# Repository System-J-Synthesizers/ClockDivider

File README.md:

# ClockDivider
DIN Sync Clock Divider

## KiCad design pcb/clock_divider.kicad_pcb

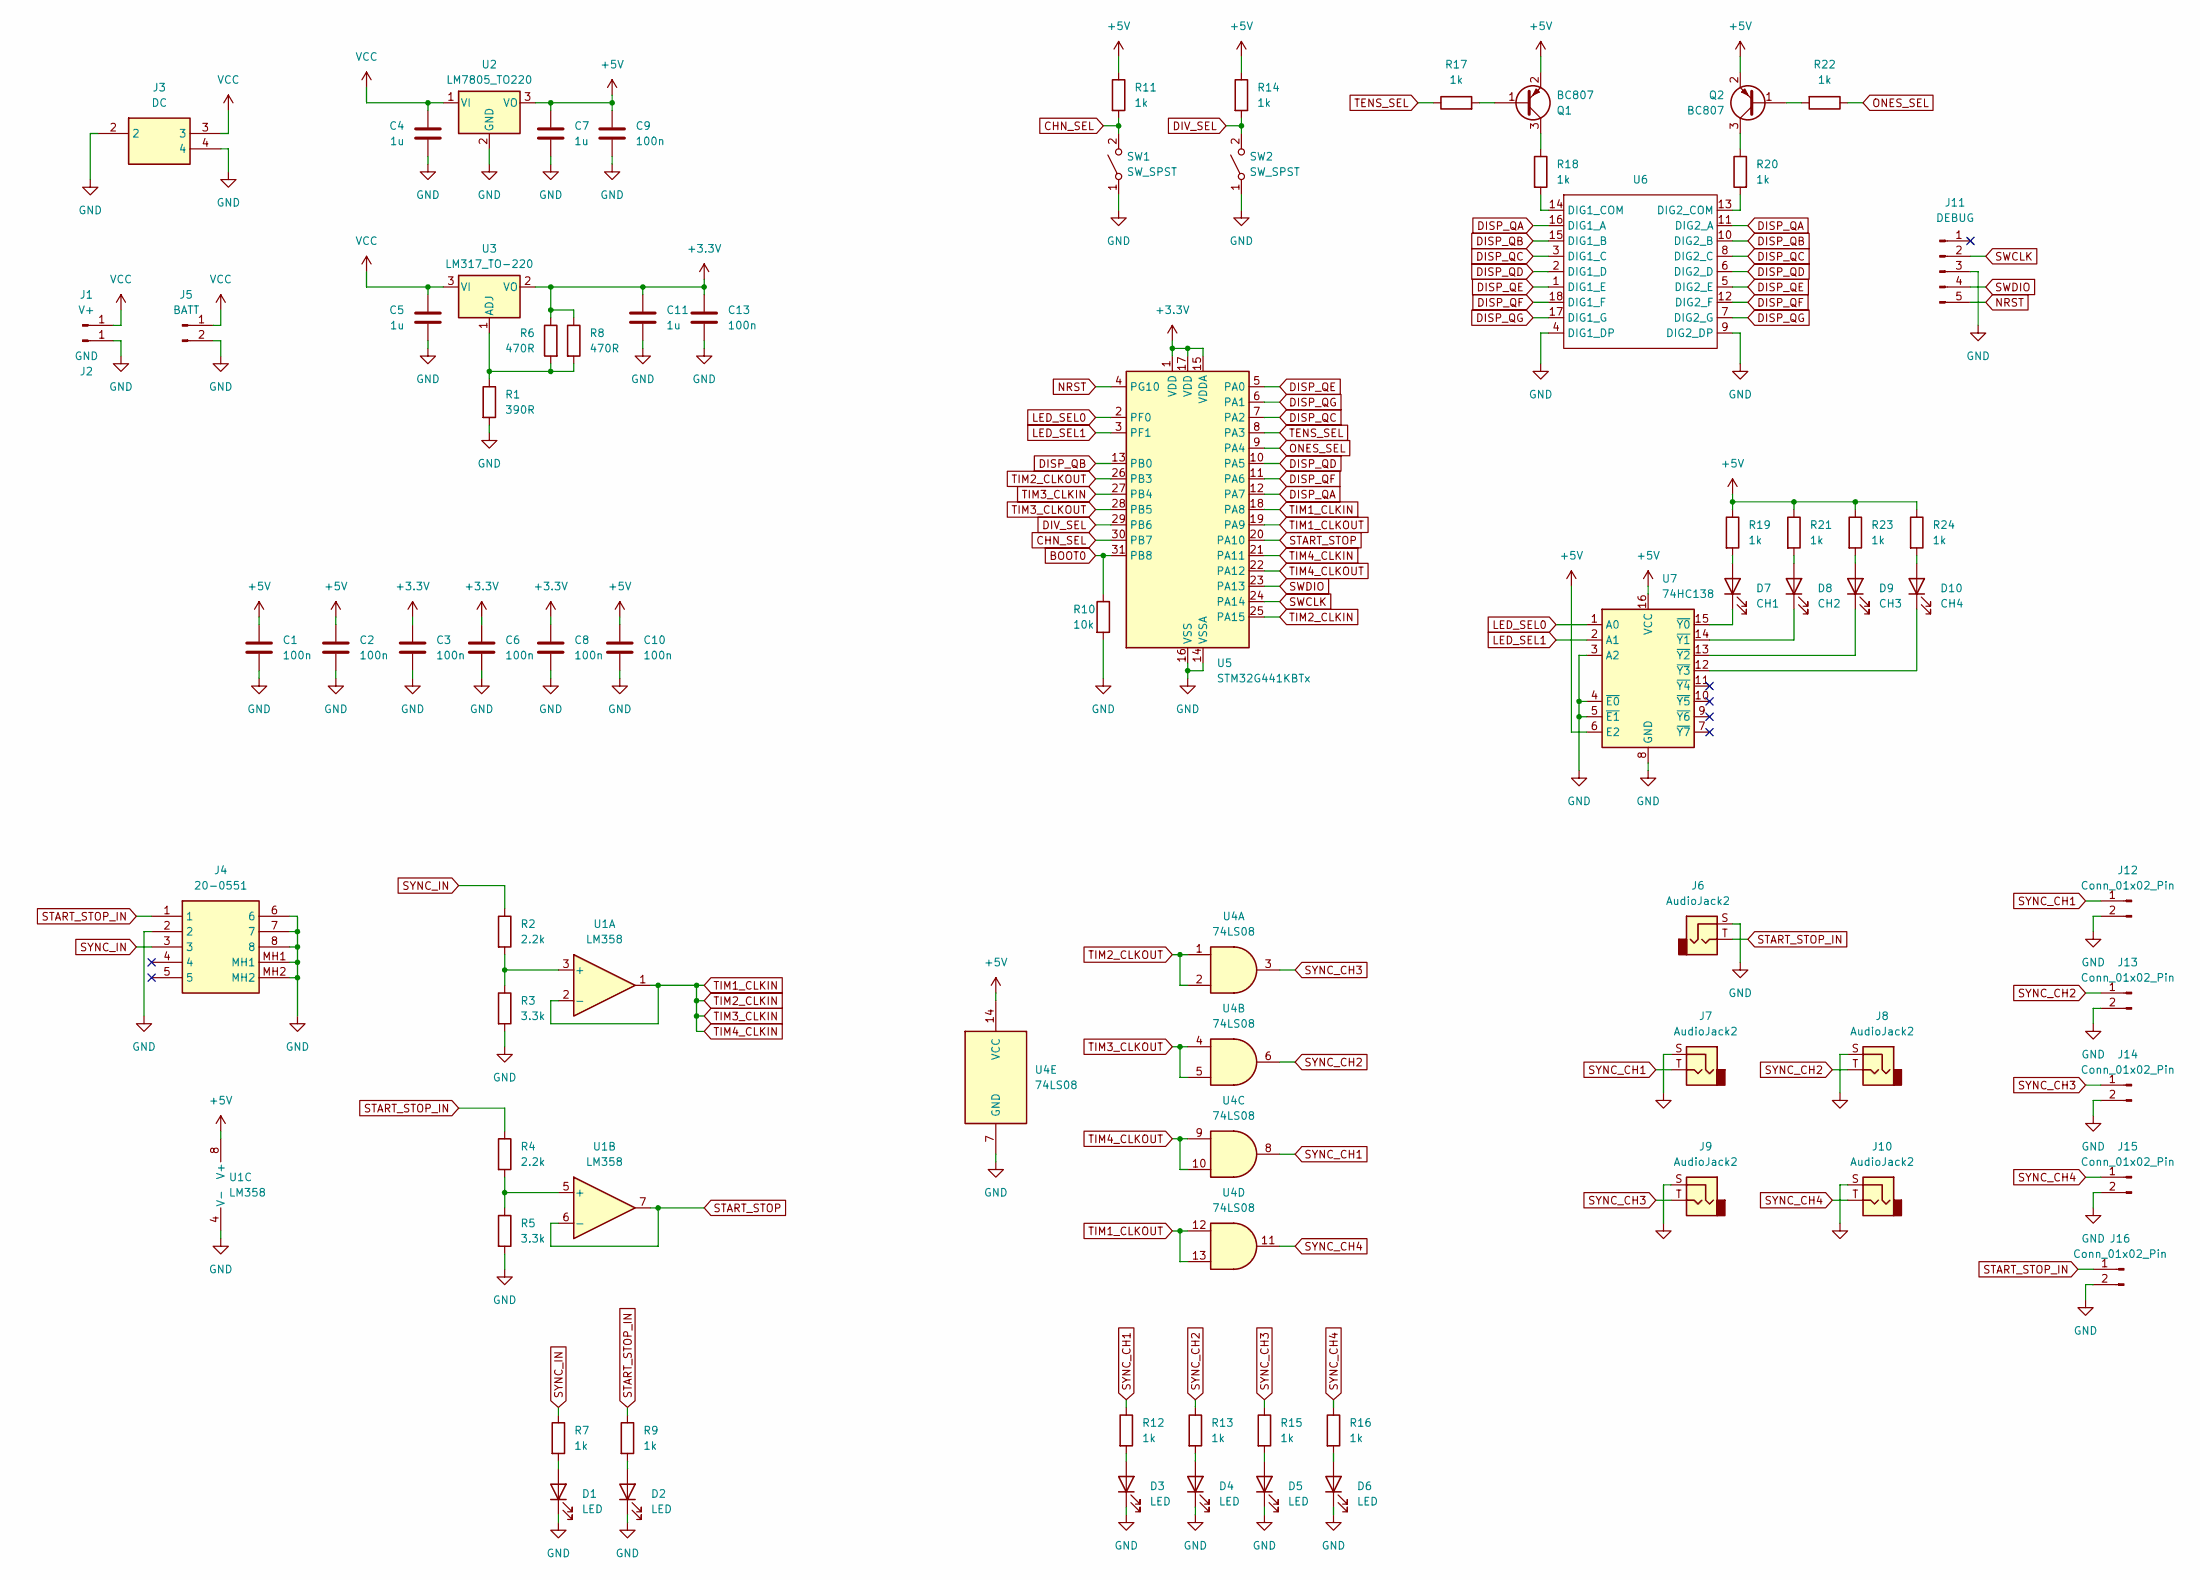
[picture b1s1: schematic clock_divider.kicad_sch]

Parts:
C1, C2, C3, C6, C8, C9, C10, C13: 100n; C_0603_1608Metric
C4, C5, C7, C11: 1u; C_0603_1608Metric
D1, D2, D3, D4, D5, D6: LED; LED_0603_1608Metric
D7: CH1; LED_0603_1608Metric
D8: CH2; LED_0603_1608Metric
D9: CH3; LED_0603_1608Metric
D10: CH4; LED_0603_1608Metric
J1: V+; PinHeader_1x01_P2.54mm_Vertical
J2: GND; PinHeader_1x01_P2.54mm_Vertical
J3: DC; 200975; Manufacturer_Part_Number 20-0975
J4: 20-0551; 200551; Manufacturer_Part_Number 20-0551
J5: BATT; PinHeader_1x02_P2.54mm_Vertical
J6, J7, J8, J9, J10: AudioJack2; Jack_3.5mm_QingPu_WQP-PJ398SM_Vertical
J11: DEBUG; PinHeader_1x05_P2.54mm_Vertical
J12, J13, J14, J15, J16: Conn_01x02_Pin; PinHeader_1x02_P2.54mm_Vertical
Q1, Q2: BC807; SOT-23
R1: 390R; R_0603_1608Metric
R2, R4: 2.2k; R_0603_1608Metric
R3, R5: 3.3k; R_0603_1608Metric
R6, R8: 470R; R_0603_1608Metric
R7, R9, R11, R12, R13, R14, R15, R16, R17, R18, R19, R20, R21, R22, R23, R24: 1k; R_0603_1608Metric
R10: 10k; R_0603_1608Metric
SW1, SW2: SW_SPST; SW_PUSH_6mm
U1: LM358; SOIC-8_3.9x4.9mm_P1.27mm
U2: LM7805_TO220; TO-220-3_Vertical
U3: LM317_TO-220; TO-220-3_Vertical
U4: 74LS08; DIP-14_W7.62mm
U5: STM32G441KBTx; LQFP-32_7x7mm_P0.8mm
U6: OSL20561
U7: 74HC138; DIP-16_W7.62mm

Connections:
+3.3V: C3.1, C6.1, C8.1, C11.1, C13.1, R6.1, R8.1, U3.2 (VO), U5.1 (VDD), U5.15 (VDDA), U5.17 (VDD)
+5V: C1.1, C2.1, C7.1, C9.1, C10.1, Q1.2 (E), Q2.2 (E), R11.1, R14.1, R19.1, R21.1, R23.1, R24.1, U1.8 (V+), U2.3 (VO), U4.14 (VCC), U7.6 (E2), U7.16 (VCC)
BOOT0: R10.1, U5.31 (PB8)
CHN_SEL: R11.2, SW1.2 (B), U5.30 (PB7)
DISP_QA: U5.12 (PA7), U6.11 (DIG2_A), U6.16 (DIG1_A)
DISP_QB: U5.13 (PB0), U6.10 (DIG2_B), U6.15 (DIG1_B)
DISP_QC: U5.7 (PA2), U6.3 (DIG1_C), U6.8 (DIG2_C)
DISP_QD: U5.10 (PA5), U6.2 (DIG1_D), U6.6 (DIG2_D)
DISP_QE: U5.5 (PA0), U6.1 (DIG1_E), U6.5 (DIG2_E)
DISP_QF: U5.11 (PA6), U6.12 (DIG2_F), U6.18 (DIG1_F)
DISP_QG: U5.6 (PA1), U6.7 (DIG2_G), U6.17 (DIG1_G)
DIV_SEL: R14.2, SW2.2 (B), U5.29 (PB6)
GND: C1.2, C2.2, C3.2, C4.2, C5.2, C6.2, C7.2, C8.2, C9.2, C10.2, C11.2, C13.2, D1.1 (K), D2.1 (K), D3.1 (K), D4.1 (K), D5.1 (K), D6.1 (K), J2.1, J3.2, J3.4, J4.2, J4.6, J4.7, J4.8, J4.MH1, J4.MH2, J5.2, J6.S, J7.S, J8.S, J9.S, J10.S, J11.3, J12.2, J13.2, J14.2, J15.2, J16.2, R1.2, R3.2, R5.2, R10.2, SW1.1 (A), SW2.1 (A), U1.4 (V-), U2.2 (GND), U4.7 (GND), U5.14 (VSSA), U5.16 (VSS), U5.32 (VSS), U6.4 (DIG1_DP), U6.9 (DIG2_DP), U7.3 (A2), U7.4 (~E0), U7.5 (~E1), U7.8 (GND)
LED_SEL0: U5.2 (PF0), U7.1 (A0)
LED_SEL1: U5.3 (PF1), U7.2 (A1)
NRST: J11.5, U5.4 (PG10)
unnamed: D1.2 (A), R7.2
unnamed: D2.2 (A), R9.2
unnamed: D3.2 (A), R12.2
unnamed: D4.2 (A), R13.2
unnamed: D5.2 (A), R15.2
unnamed: D6.2 (A), R16.2
unnamed: D7.2 (A), R19.2
unnamed: D7.1 (K), U7.15 (~Y0)
unnamed: D8.2 (A), R21.2
unnamed: D8.1 (K), U7.14 (~Y1)
unnamed: D9.2 (A), R23.2
unnamed: D9.1 (K), U7.13 (~Y2)
unnamed: D10.2 (A), R24.2
unnamed: D10.1 (K), U7.12 (~Y3)
unnamed: Q1.1 (B), R17.2
unnamed: Q1.3 (C), R18.1
unnamed: Q2.1 (B), R22.2
unnamed: Q2.3 (C), R20.1
unnamed: R2.2, R3.1, U1.3 (+)
unnamed: R4.2, R5.1, U1.5 (+)
unnamed: R1.1, R6.2, R8.2, U3.1 (ADJ)
unnamed: R18.2, U6.14 (DIG1_COM)
unnamed: R20.2, U6.13 (DIG2_COM)
ONES_SEL: R22.1, U5.9 (PA4)
START_STOP: U1.6 (-), U1.7, U5.20 (PA10)
START_STOP_IN: J4.1, J6.T, J16.1, R4.1, R9.1
SWCLK: J11.2, U5.24 (PA14)
SWDIO: J11.4, U5.23 (PA13)
SYNC_CH1: J7.T, J12.1, R12.1, U4.8
SYNC_CH2: J8.T, J13.1, R13.1, U4.6
SYNC_CH3: J9.T, J14.1, R15.1, U4.3
SYNC_CH4: J10.T, J15.1, R16.1, U4.11
SYNC_IN: J4.3, R2.1, R7.1
TENS_SEL: R17.1, U5.8 (PA3)
TIM1_CLKIN: U1.1, U1.2 (-), U5.18 (PA8), U5.21 (PA11), U5.25 (PA15), U5.27 (PB4)
TIM1_CLKOUT: U4.12, U4.13, U5.19 (PA9)
TIM2_CLKOUT: U4.1, U4.2, U5.26 (PB3)
TIM3_CLKOUT: U4.4, U4.5, U5.28 (PB5)
TIM4_CLKOUT: U4.9, U4.10, U5.22 (PA12)
VCC: C4.1, C5.1, J1.1, J3.3, J5.1, U2.1 (VI), U3.3 (VI)

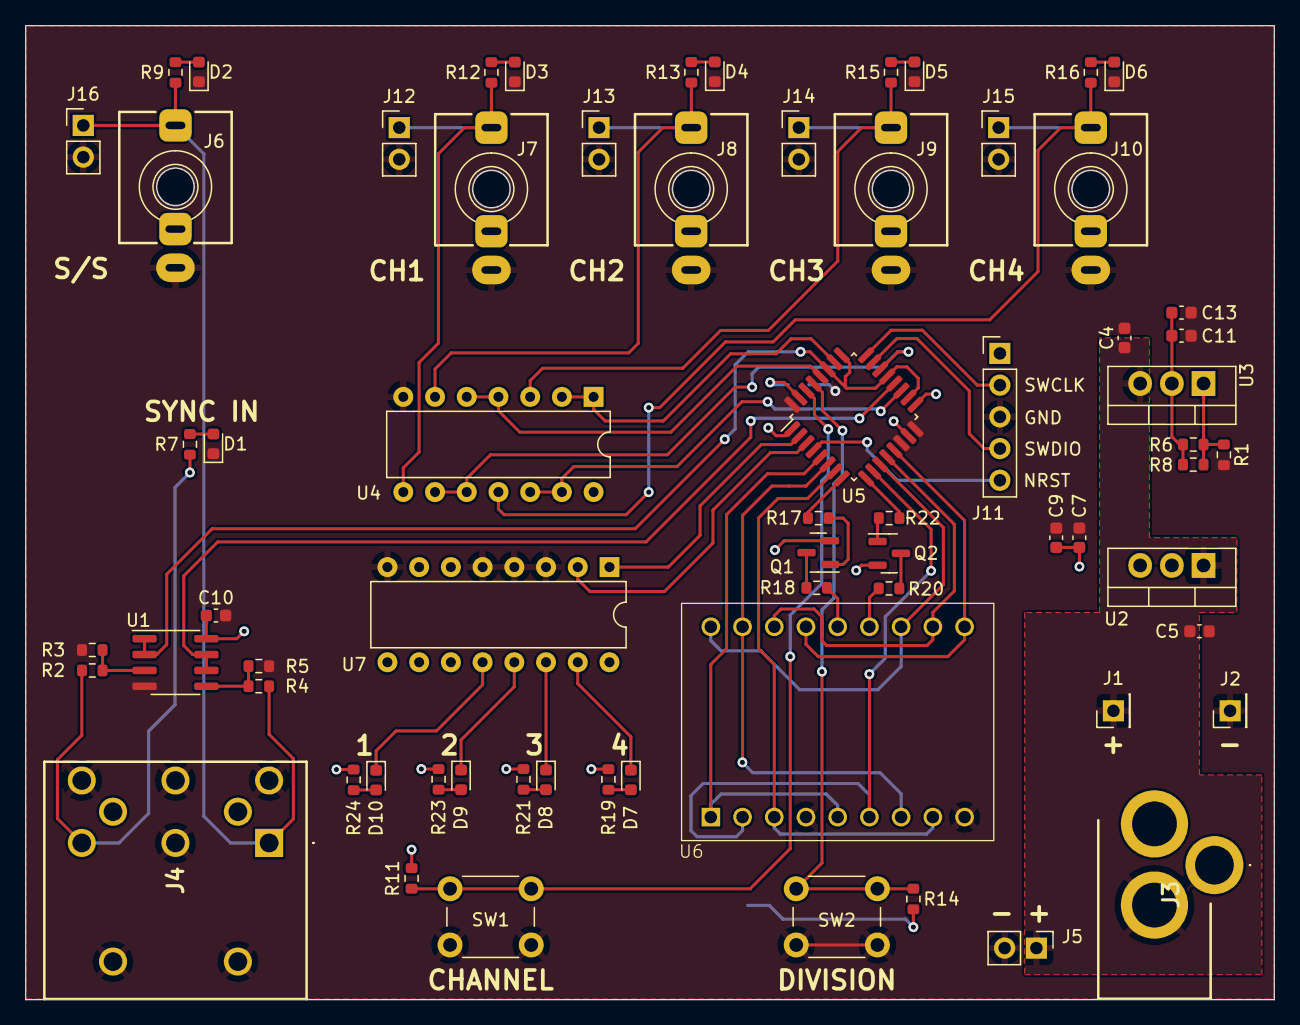
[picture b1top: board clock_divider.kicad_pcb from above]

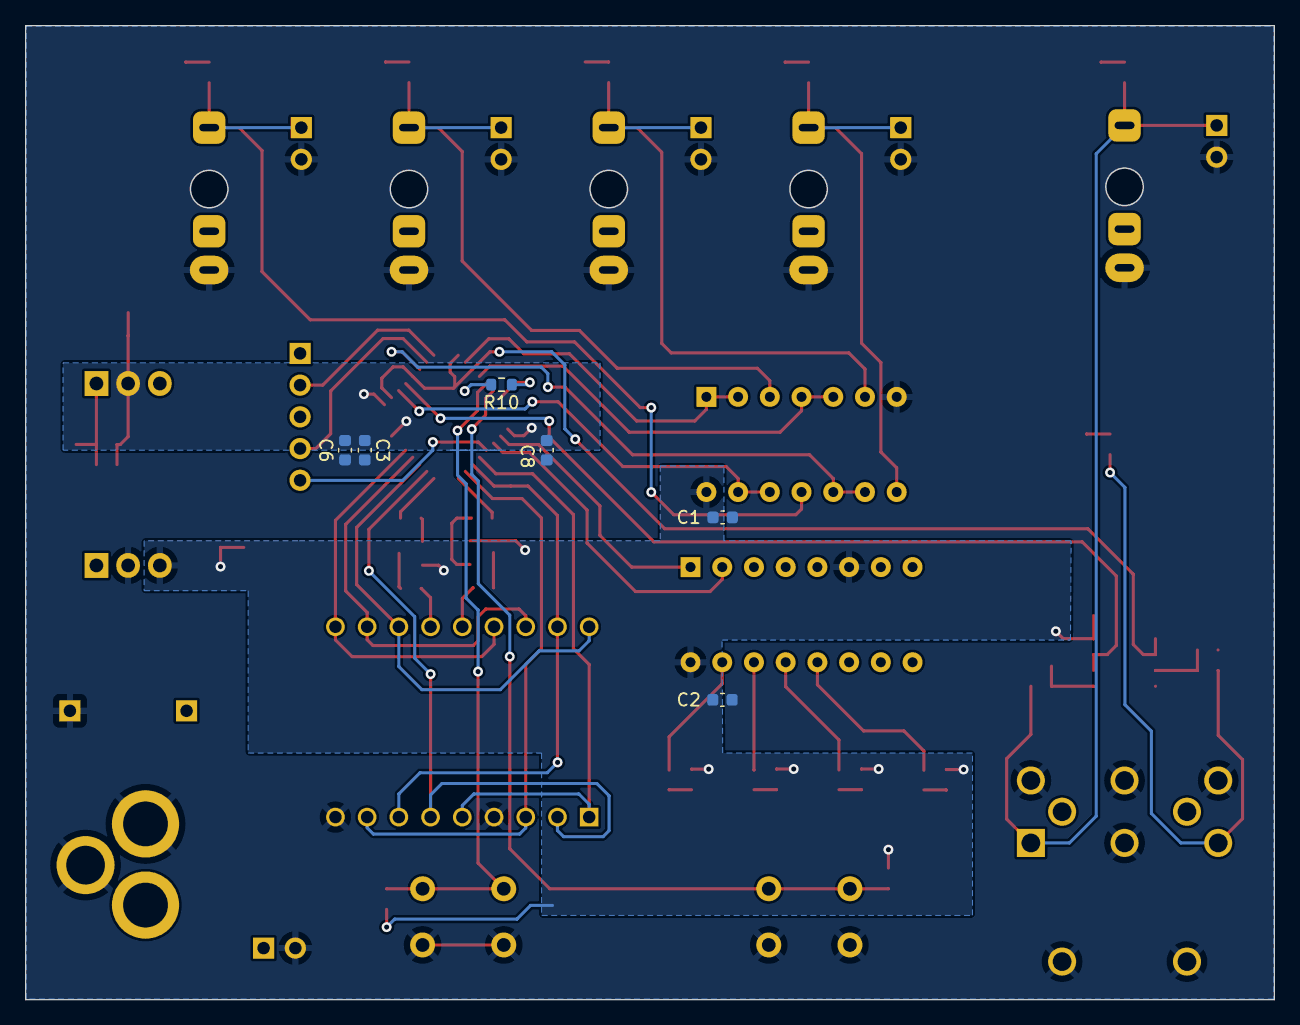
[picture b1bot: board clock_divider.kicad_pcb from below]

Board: 2 copper layers, 100.0 x 78.0 mm, 73 parts (6 on the bottom side), 56 nets.

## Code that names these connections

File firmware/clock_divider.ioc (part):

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Mcu.Name=STM32G441KBTx
Mcu.Package=LQFP32
Mcu.UserName=STM32G441KBTx
PA0.GPIOParameters=GPIO_Label
PA0.GPIO_Label=DISP_QA
PA0.Signal=GPIO_Output
PA1.GPIOParameters=GPIO_Label
PA1.GPIO_Label=DISP_QB
PA1.Signal=GPIO_Output
PA10.GPIOParameters=GPIO_Label
PA10.GPIO_Label=START_STOP
PA10.Signal=GPIO_Input
PA11.GPIOParameters=GPIO_Label
PA11.GPIO_Label=TIM4_CLKIN
PA11.Signal=S_TIM4_CH1
PA12.GPIOParameters=GPIO_Label
PA12.GPIO_Label=TIM4_CLKOUT
PA12.Signal=S_TIM4_CH2
PA13.GPIOParameters=GPIO_Label
PA13.GPIO_Label=SWDIO
PA13.Mode=Serial_Wire
PA13.Signal=SYS_JTMS-SWDIO
PA14.GPIOParameters=GPIO_Label
PA14.GPIO_Label=SWCLK
PA14.Mode=Serial_Wire
PA14.Signal=SYS_JTCK-SWCLK
PA15.GPIOParameters=GPIO_Label
PA15.GPIO_Label=TIM2_CLKIN
PA15.Signal=S_TIM2_CH1
PA2.GPIOParameters=GPIO_Label
PA2.GPIO_Label=DISP_QC
PA2.Signal=GPIO_Output
PA3.GPIOParameters=GPIO_Label
PA3.GPIO_Label=TENS_SEL
PA3.Signal=GPIO_Output
PA4.GPIOParameters=GPIO_Label
PA4.GPIO_Label=ONES_SEL
PA4.Signal=GPIO_Output
PA5.GPIOParameters=GPIO_Label
PA5.GPIO_Label=DISP_QD
PA5.Signal=GPIO_Output
PA6.GPIOParameters=GPIO_Label
PA6.GPIO_Label=DISP_QE
PA6.Signal=GPIO_Output
PA7.GPIOParameters=GPIO_Label
PA7.GPIO_Label=DISP_QF
PA7.Signal=GPIO_Output
PA8.GPIOParameters=GPIO_Label
PA8.GPIO_Label=TIM1_CLKIN
PA8.Signal=S_TIM1_CH1
PA9.GPIOParameters=GPIO_Label
PA9.GPIO_Label=TIM1_CLKOUT
PA9.Signal=S_TIM1_CH2
PB0.GPIOParameters=GPIO_Label
PB0.GPIO_Label=DISP_QG
PB0.Signal=GPIO_Output
PB3.GPIOParameters=GPIO_Label
PB3.GPIO_Label=TIM2_CLKOUT
PB3.Signal=S_TIM2_CH2
PB4.GPIOParameters=GPIO_Label
PB4.GPIO_Label=TIM3_CLKIN
PB4.Signal=S_TIM3_CH1
PB5.GPIOParameters=GPIO_Label
PB5.GPIO_Label=TIM3_CLKOUT
PB5.Signal=S_TIM3_CH2
PB6.GPIOParameters=GPIO_Label
PB6.GPIO_Label=CHN_SEL
PB6.Signal=GPIO_Input
PB7.GPIOParameters=GPIO_Label
PB7.GPIO_Label=DIV_SEL
PB7.Signal=GPIO_Input
PB8-BOOT0.GPIOParameters=GPIO_Label
PB8-BOOT0.GPIO_Label=BOOT0
PB8-BOOT0.Signal=GPIO_Input
PF0-OSC_IN.GPIOParameters=GPIO_Label
PF0-OSC_IN.GPIO_Label=LED_SEL0
PF0-OSC_IN.Signal=GPIO_Output
PF1-OSC_OUT.GPIOParameters=GPIO_Label
PF1-OSC_OUT.GPIO_Label=LED_SEL1
PF1-OSC_OUT.Signal=GPIO_Output
PG10-NRST.GPIOParameters=GPIO_Label
PG10-NRST.GPIO_Label=NRST
PG10-NRST.Signal=GPIO_Input
RCC.HSE_VALUE=8000000
RCC.SYSCLKFreq_VALUE=16000000
board=custom

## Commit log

2023-11-15 move outputs to pcb
2023-11-15 move ioc to firmware
2023-11-15 remove old pdf
2023-11-26 updates for today
